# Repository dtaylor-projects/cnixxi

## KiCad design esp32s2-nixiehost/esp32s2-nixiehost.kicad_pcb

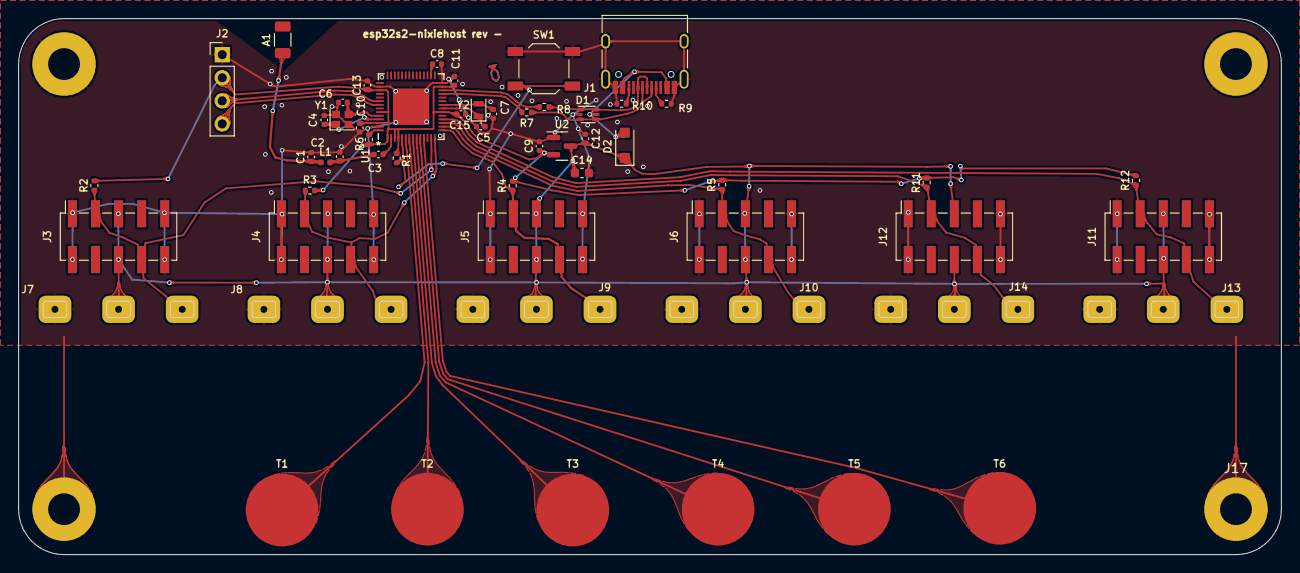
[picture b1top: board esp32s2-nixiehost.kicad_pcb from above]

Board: 2 copper layers, 139.0 x 59.0 mm, 60 parts (0 on the bottom side), 34 nets.

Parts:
A1: ANT; R_1206_3216Metric
C1, C2: NP; C_0402_1005Metric
C3, C4, C5, C6, C7: 10p; C_0402_1005Metric
C8, C12: 1u; C_0402_1005Metric
C9: 10u; C_0402_1005Metric
C10, C11, C13, C15: 0.1u16v; C_0402_1005Metric
C14: 10u; C_0603_1608Metric
D1: USBLC6-2P6-TVS; SOT-666
D2: SCH; D_SOD-123F
J1: USB_C_Receptacle_USB2.0; USB_C_Receptacle_HRO_TYPE-C-31-M-12
J2: PGM; PinHeader_1x04_P2.54mm_Vertical
J3: OUTPUTPINS0; PinSocket_2x05_P2.54mm_Vertical_SMD
J4: OUTPUTPINS1; PinSocket_2x05_P2.54mm_Vertical_SMD
J5: OUTPUTPINS2; PinSocket_2x05_P2.54mm_Vertical_SMD
J6: OUTPUTPINS3; PinSocket_2x05_P2.54mm_Vertical_SMD
J7: OUTPUTSLOTS0; nixiehostslot
J8: OUTPUTSLOTS1; nixiehostslot
J9: OUTPUTSLOTS2; nixiehostslot
J10: OUTPUTSLOTS3; nixiehostslot
J11: OUTPUTPINS5; PinSocket_2x05_P2.54mm_Vertical_SMD
J12: OUTPUTPINS4; PinSocket_2x05_P2.54mm_Vertical_SMD
J13: OUTPUTSLOTS5; nixiehostslot
J14: OUTPUTSLOTS4; nixiehostslot
J15, J16, J17, J18: MountingHole_3.5mm_Pad
L1: 6.8nH; L_0402_1005Metric
R1, R6, R9, R10: 5.1k; R_0402_1005Metric
R2, R3, R4, R5, R11, R12: 10k; R_0402_1005Metric
R7, R8: 22; R_0402_1005Metric
SW1: TS-1187A-B-A-B; SW_SPST_TL3342
T1, T2, T3, T4, T5, T6: TOUCH; TouchExposed6
U1: ESP32-S2; ESP32S2
U2: ME6206A36M3G; SOT-23
Y1: 40MHz; Crystal_SMD_2016-4Pin_2.0x1.6mm
Y2: 32.786k; Crystal_SMD_2012-2Pin_2.0x1.2mm

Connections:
CHIP_PU: R6.1, U1.56 (CHIP_PU)
D+: D1.1 (IO1), D1.6 (IO1), J1.A6 (D+), J1.B6 (D+), R8.2
D-: D1.3 (IO2), D1.4 (IO2), J1.A7 (D-), J1.B7 (D-), R7.1
GND: C1.2, C2.2, C4.1, C5.1, C6.1, C7.1, C8.2, C9.2, C10.2, C11.2, C12.1, C13.2, C14.2, C15.2, D1.2 (GND), J1.A1 (GND), J1.A12 (GND), J1.B1 (GND), J1.B12 (GND), J1.S1 (SHIELD), J2.1, J3.1, J3.2, J3.9, J3.10, J4.1, J4.2, J4.9, J4.10, J5.1, J5.2, J5.9, J5.10, J6.1, J6.2, J6.9, J6.10, J7.1, J8.1, J9.1, J10.1, J11.1, J11.2, J11.9, J11.10, J12.1, J12.2, J12.9, J12.10, J13.1, J14.1, J15.1, J16.1, J17.1, J18.1, R9.2, R10.2, SW1.1 (A), U1.28 (GPIO21), U1.44 (MTDO0), U1.55 (GPIO46), U1.57 (GND), U2.1 (GND), Y1.2, Y1.4
GPIO0: R1.2, SW1.2 (B), U1.5 (GPIO0)
LEDCTL0: J3.3, J3.8, J7.3, R2.1, U1.13 (GPIO8)
LEDCTL1: J4.3, J4.8, J8.3, R3.1, U1.14 (GPIO9)
LEDCTL2: J5.3, J5.8, J9.3, R4.1, U1.15 (GPIO10)
LEDCTL3: J6.3, J6.8, J10.3, R5.1, U1.16 (GPIO11)
LEDCTL4: J12.3, J12.8, J14.3, R11.1, U1.17 (GPIO12)
LEDCTL5: J11.3, J11.8, J13.3, R12.1, U1.18 (GPIO13)
unnamed: A1.1, C1.1, L1.1
unnamed: C2.1, C3.1, L1.2
unnamed: C3.2, U1.2 (LNA_IN)
unnamed: C4.2, U1.53 (XTAL_P), Y1.1
unnamed: C5.2, U1.21 (XTAL_32K_P), Y2.1
unnamed: C6.2, U1.52 (XTAL_N), Y1.3
unnamed: C7.2, U1.22 (XTAL_32K_N), Y2.2
unnamed: C8.1, U1.30 (VDD_SPI)
unnamed: J1.A5 (CC1), R9.1
unnamed: J1.B5 (CC2), R10.1
unnamed: R7.2, U1.25 (GPIO19)
unnamed: R8.1, U1.26 (GPIO20)
unnamed: T1.1, U1.6 (GPIO1)
unnamed: T2.1, U1.7 (GPIO2)
unnamed: T3.1, U1.8 (GPIO3)
unnamed: T4.1, U1.9 (GPIO4)
unnamed: T5.1, U1.10 (GPIO5)
unnamed: T6.1, U1.11 (GPIO6)
RX: J2.4, U1.49 (U0XD)
TX: J2.3, U1.48 (U0TXD)
USBBUS: D1.5 (VB), D2.2 (A), J1.A4 (VBUS), J1.A9 (VBUS), J1.B4 (VBUS), J1.B9 (VBUS)
VBUS: C12.2, C14.1, D2.1 (K), J3.5, J3.6, J4.5, J4.6, J5.5, J5.6, J6.5, J6.6, J7.2, J8.2, J9.2, J10.2, J11.5, J11.6, J12.5, J12.6, J13.2, J14.2, U2.3 (VI)
VDD: C9.1, C10.1, C11.1, C13.1, C15.1, J2.2, R1.1, R2.2, R3.2, R4.2, R5.2, R6.2, R11.2, R12.2, U1.1 (VDDA), U1.3 (VDD3P3), U1.4 (VDD3P3), U1.20 (V333P3_RTC), U1.27 (VDD3P3_RTC_IO), U1.45 (VDD3P3_CPU), U1.51 (VDDA), U1.54 (VDDA), U2.2 (VO)

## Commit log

2025-03-07 Add initial fp-info-cache and update KiCad project files with new settings
